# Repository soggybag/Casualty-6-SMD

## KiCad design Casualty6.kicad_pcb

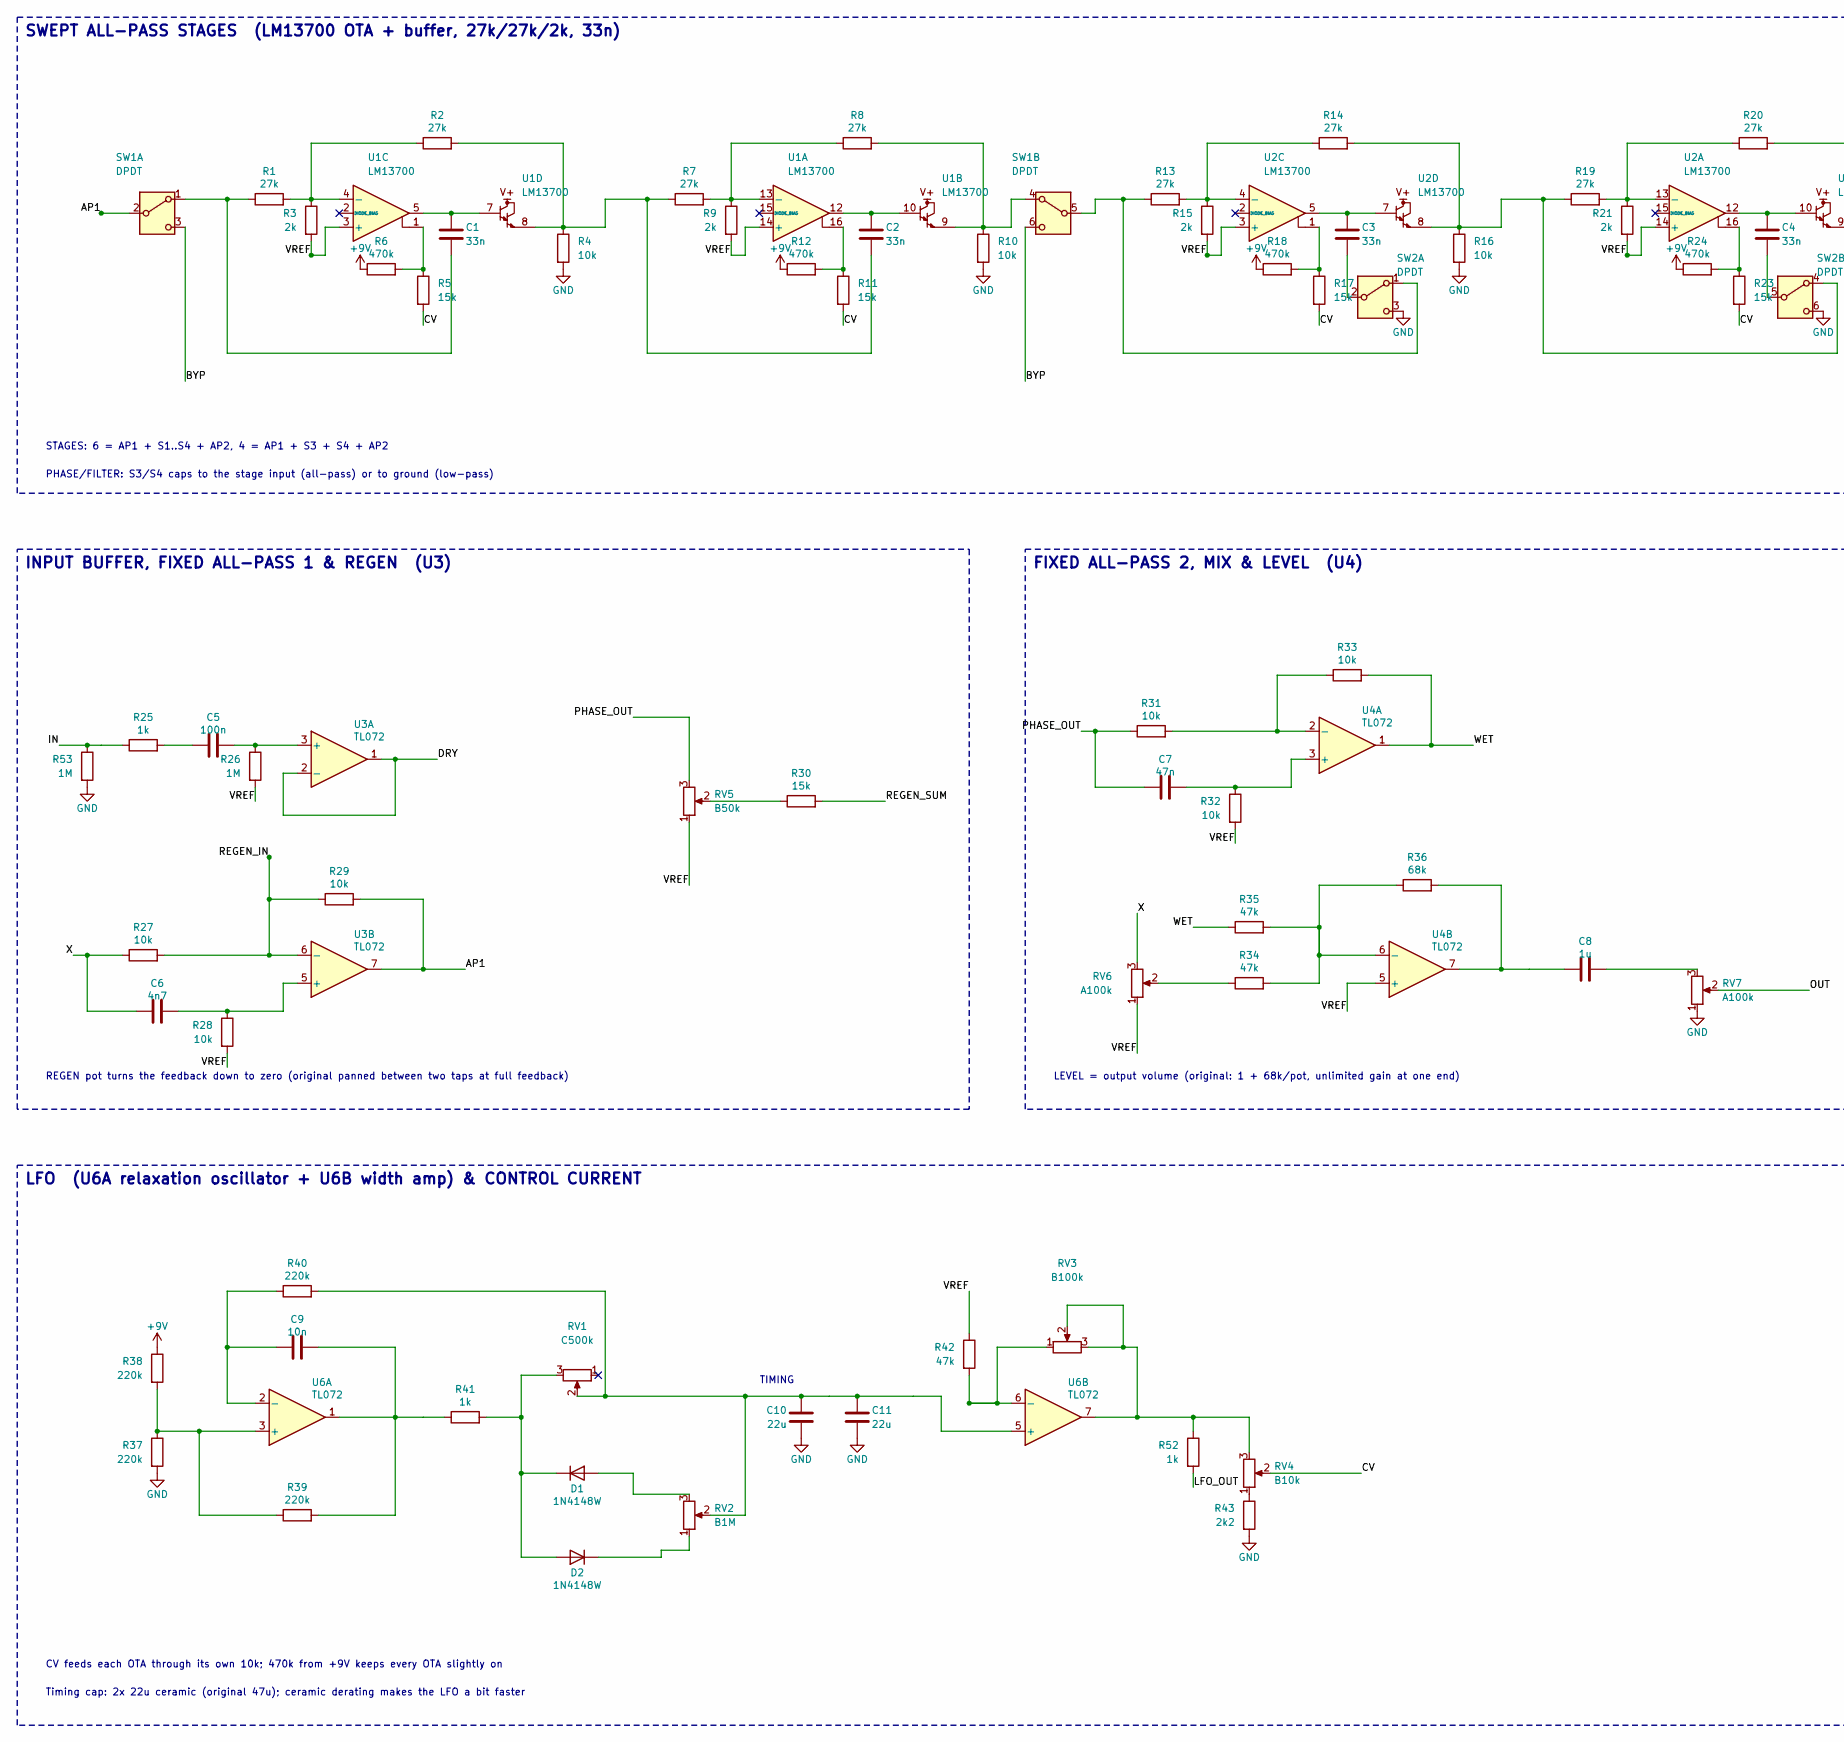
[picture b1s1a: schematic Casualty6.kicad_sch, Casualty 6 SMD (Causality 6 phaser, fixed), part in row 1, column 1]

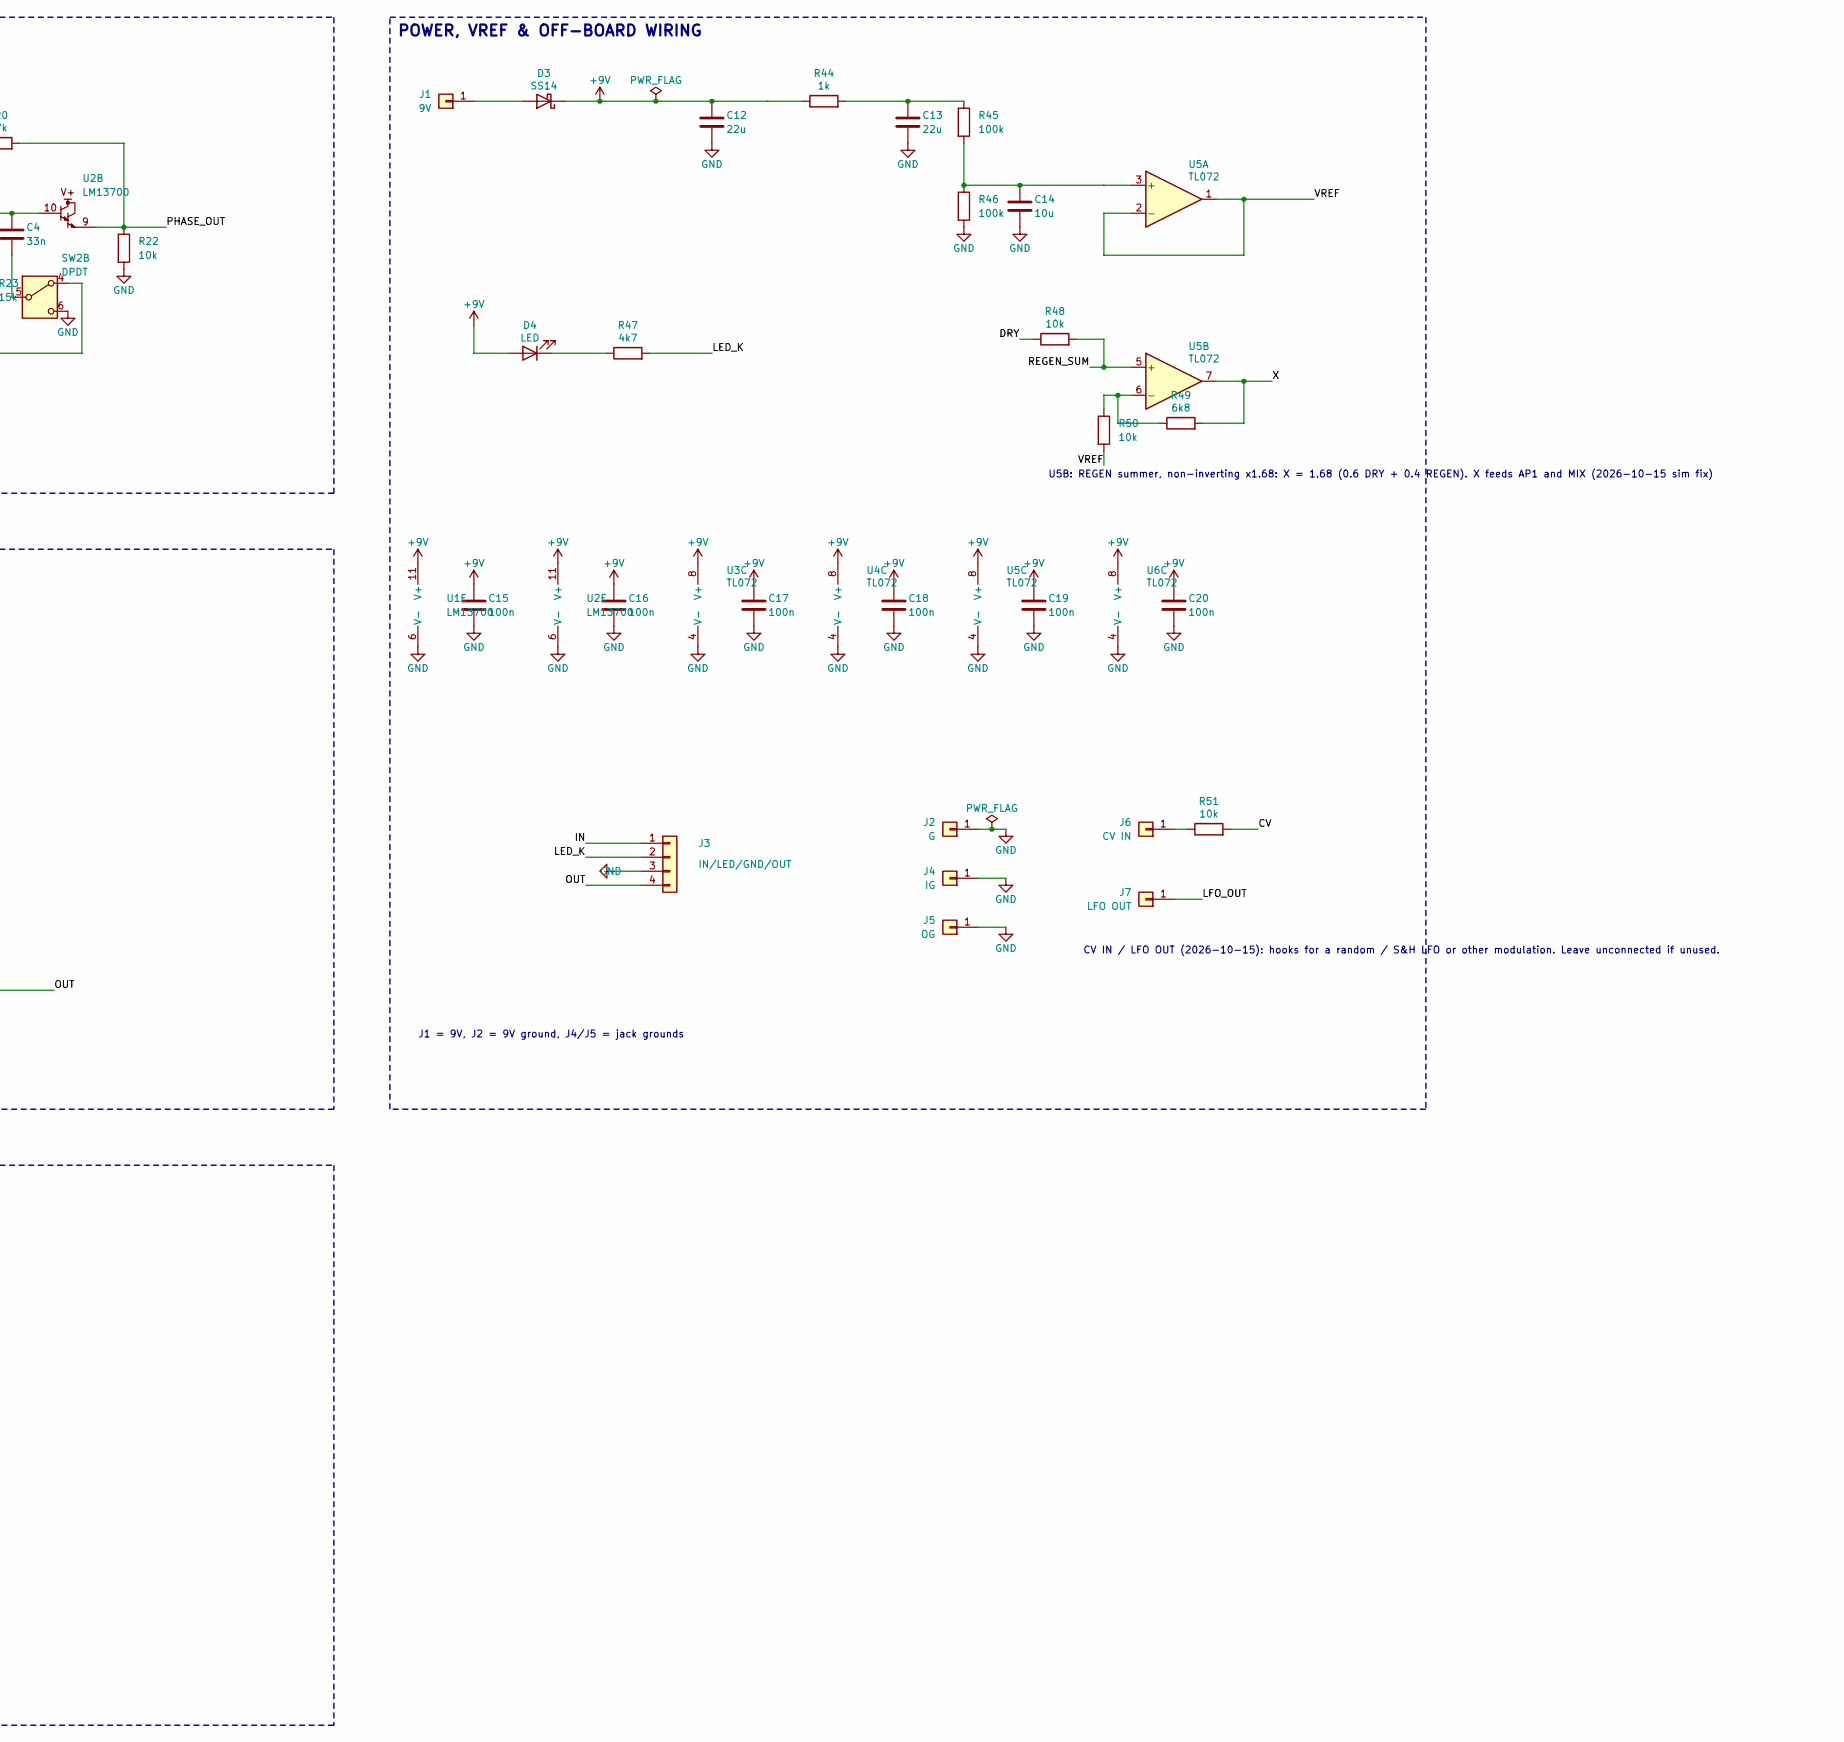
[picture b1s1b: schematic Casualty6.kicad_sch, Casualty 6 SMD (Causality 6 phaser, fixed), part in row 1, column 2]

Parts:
C1, C2, C3, C4: 33n; C_0805_2012Metric_Pad1.18x1.45mm_HandSolder; LCSC C1739
C5, C15, C16, C17, C18, C19, C20: 100n; C_0805_2012Metric_Pad1.18x1.45mm_HandSolder; LCSC C49678
C6: 4n7; C_0805_2012Metric_Pad1.18x1.45mm_HandSolder; LCSC C1744
C7: 47n; C_0805_2012Metric_Pad1.18x1.45mm_HandSolder; LCSC C53134
C8: 1u; C_0805_2012Metric_Pad1.18x1.45mm_HandSolder; LCSC C28323
C9: 10n; C_0805_2012Metric_Pad1.18x1.45mm_HandSolder; LCSC C1710
C10, C11, C12, C13: 22u; C_1206_3216Metric_Pad1.33x1.80mm_HandSolder; LCSC C12891
C14: 10u; C_0805_2012Metric_Pad1.18x1.45mm_HandSolder; LCSC C15850
D1, D2: 1N4148W; D_SOD-123; LCSC C81598
D3: SS14; D_SMA_Handsoldering; LCSC C2480
D4: LED; LED_D3.0mm
J1: 9V; SolderWire-0.5sqmm_1x01_D0.9mm_OD2.1mm
J2: G; SolderWire-0.5sqmm_1x01_D0.9mm_OD2.1mm
J3: IN/LED/GND/OUT; PinHeader_1x04_P2.54mm_Vertical
J4: IG; SolderWire-0.5sqmm_1x01_D0.9mm_OD2.1mm
J5: OG; SolderWire-0.5sqmm_1x01_D0.9mm_OD2.1mm
J6: CV IN; SolderWire-0.5sqmm_1x01_D0.9mm_OD2.1mm
J7: LFO OUT; SolderWire-0.5sqmm_1x01_D0.9mm_OD2.1mm
R1, R2, R7, R8, R13, R14, R19, R20: 27k; R_0805_2012Metric_Pad1.20x1.40mm_HandSolder; LCSC C17593
R3, R9, R15, R21: 2k; R_0805_2012Metric_Pad1.20x1.40mm_HandSolder; LCSC C17604
R4, R10, R16, R22, R27, R28, R29, R31, R32, R33, R48, R50, R51: 10k; R_0805_2012Metric_Pad1.20x1.40mm_HandSolder; LCSC C17414
R5, R11, R17, R23, R30: 15k; R_0805_2012Metric_Pad1.20x1.40mm_HandSolder; LCSC C17475
R6, R12, R18, R24: 470k; R_0805_2012Metric_Pad1.20x1.40mm_HandSolder; LCSC C17709
R25, R41, R44, R52: 1k; R_0805_2012Metric_Pad1.20x1.40mm_HandSolder; LCSC C17513
R26, R53: 1M; R_0805_2012Metric_Pad1.20x1.40mm_HandSolder; LCSC C17514
R34, R35, R42: 47k; R_0805_2012Metric_Pad1.20x1.40mm_HandSolder; LCSC C17713
R36: 68k; R_0805_2012Metric_Pad1.20x1.40mm_HandSolder; LCSC C17801
R37, R38, R39, R40: 220k; R_0805_2012Metric_Pad1.20x1.40mm_HandSolder; LCSC C17556
R43: 2k2; R_0805_2012Metric_Pad1.20x1.40mm_HandSolder; LCSC C17520
R45, R46: 100k; R_0805_2012Metric_Pad1.20x1.40mm_HandSolder; LCSC C149504
R47: 4k7; R_0805_2012Metric_Pad1.20x1.40mm_HandSolder; LCSC C17673
R49: 6k8; R_0805_2012Metric_Pad1.20x1.40mm_HandSolder; LCSC C17772
RV1: C500k; Potentiometer_Alpha_16mm_Vertical
RV2: B1M; Potentiometer_Alpha_16mm_Vertical
RV3: B100k; Potentiometer_Alpha_16mm_Vertical
RV4: B10k; Potentiometer_Alpha_16mm_Vertical
RV5: B50k; Potentiometer_Alpha_16mm_Vertical
RV6, RV7: A100k; Potentiometer_Alpha_16mm_Vertical
SW1, SW2: DPDT; SW_Taiway_100_DPDT_PC
U1, U2: LM13700; SOIC-16_3.9x9.9mm_P1.27mm; LCSC C1346265
U3, U4, U5, U6: TL072; SOIC-8_3.9x4.9mm_P1.27mm; LCSC C6961

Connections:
/AP1: R29.2, SW1.2 (B), U3.7
/BYP: SW1.3 (C), SW1.6 (C)
/CV: R5.2, R11.2, R17.2, R23.2, R51.2, RV4.2
/DRY: R48.1, U3.1, U3.2 (-)
/IN: J3.1, R25.1, R53.1
/LED_K: J3.2, R47.2
/LFO_OUT: J7.1, R52.2
/OUT: J3.4, RV7.2
/PHASE_OUT: C7.1, R20.2, R22.1, R31.1, RV5.3, U2.9
/REGEN_IN: R27.2, R29.1, U3.6 (-)
/REGEN_SUM: R30.2, R48.2, U5.5 (+)
/VREF: R3.2, R9.2, R15.2, R21.2, R26.2, R28.2, R32.2, R42.1, R50.2, RV5.1, RV6.1, U1.3 (+), U1.14 (+), U2.3 (+), U2.14 (+), U4.5 (+), U5.1, U5.2 (-)
/WET: R33.2, R35.1, U4.1
/X: C6.1, R27.1, R49.2, RV6.3, U5.7
unnamed: C1.1, U1.5, U1.7
unnamed: C2.1, U1.10, U1.12
unnamed: C2.2, R2.2, R4.1, R7.1, U1.8
unnamed: C3.1, U2.5, U2.7
unnamed: C4.1, U2.10, U2.12
unnamed: C5.1, R25.2
unnamed: C8.1, R36.2, U4.7
unnamed: C8.2, RV7.3
unnamed: C9.2, R39.2, R41.1, U6.1
unnamed: C13.1, R44.2, R45.1
unnamed: D1.2 (A), RV2.3
unnamed: D1.1 (K), D2.2 (A), R41.2, RV1.3
unnamed: D2.1 (K), RV2.1
unnamed: D3.2 (A), J1.1
unnamed: D4.1 (K), R47.1
unnamed: J6.1, R51.1
unnamed: R5.1, R6.2, U1.1
unnamed: R11.1, R12.2, U1.16
unnamed: R17.1, R18.2, U2.1
unnamed: R23.1, R24.2, U2.16
unnamed: R30.1, RV5.2
unnamed: R34.1, RV6.2
unnamed: R43.1, RV4.1
unnamed: R52.1, RV3.2, RV3.3, RV4.3, U6.7
unnamed: C1.2, R1.1, SW1.1 (A)
unnamed: R8.2, R10.1, SW1.4 (A), U1.9
unnamed: R13.1, SW1.5 (B), SW2.1 (A)
unnamed: C3.2, SW2.2 (B)
unnamed: R14.2, R16.1, R19.1, SW2.4 (A), U2.8
unnamed: C4.2, SW2.5 (B)
unnamed: R7.2, R8.1, R9.1, U1.13 (-)
unnamed: R1.2, R2.1, R3.1, U1.4 (-)
unnamed: R19.2, R20.1, R21.1, U2.13 (-)
unnamed: R13.2, R14.1, R15.1, U2.4 (-)
unnamed: C5.2, R26.1, U3.3 (+)
unnamed: C6.2, R28.1, U3.5 (+)
unnamed: C7.2, R32.1, U4.3 (+)
unnamed: R31.2, R33.1, U4.2 (-)
unnamed: R34.2, R35.2, R36.1, U4.6 (-)
unnamed: C14.1, R45.2, R46.1, U5.3 (+)
unnamed: R49.1, R50.1, U5.6 (-)
unnamed: R37.1, R38.2, R39.1, U6.3 (+)
unnamed: C9.1, R40.1, U6.2 (-)
unnamed: C10.1, C11.1, R40.2, RV1.2, RV2.2, U6.5 (+)
unnamed: R42.2, RV3.1, U6.6 (-)

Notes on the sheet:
CV IN / LFO OUT (2026-10-15): hooks for a random / S&H LFO or other modulation. Leave unconnected if unused.
SWEPT ALL-PASS STAGES (LM13700 OTA + buffer, 27k/27k/2k, 33n)
STAGES: 6 = AP1 + S1..S4 + AP2, 4 = AP1 + S3 + S4 + AP2
PHASE/FILTER: S3/S4 caps to the stage input (all-pass) or to ground (low-pass)
INPUT BUFFER, FIXED ALL-PASS 1 & REGEN (U3)
REGEN pot turns the feedback down to zero (original panned between two taps at full feedback)
FIXED ALL-PASS 2, MIX & LEVEL (U4)
LEVEL = output volume (original: 1 + 68k/pot, unlimited gain at one end)
LFO (U6A relaxation oscillator + U6B width amp) & CONTROL CURRENT
TIMING
CV feeds each OTA through its own 10k; 470k from +9V keeps every OTA slightly on
Timing cap: 2x 22u ceramic (original 47u); ceramic derating makes the LFO a bit faster
POWER, VREF & OFF-BOARD WIRING
U5B: REGEN summer, non-inverting x1.68: X = 1.68 (0.6 DRY + 0.4 REGEN). X feeds AP1 and MIX (2026-10-15 sim fix)
J1 = 9V, J2 = 9V ground, J4/J5 = jack grounds

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
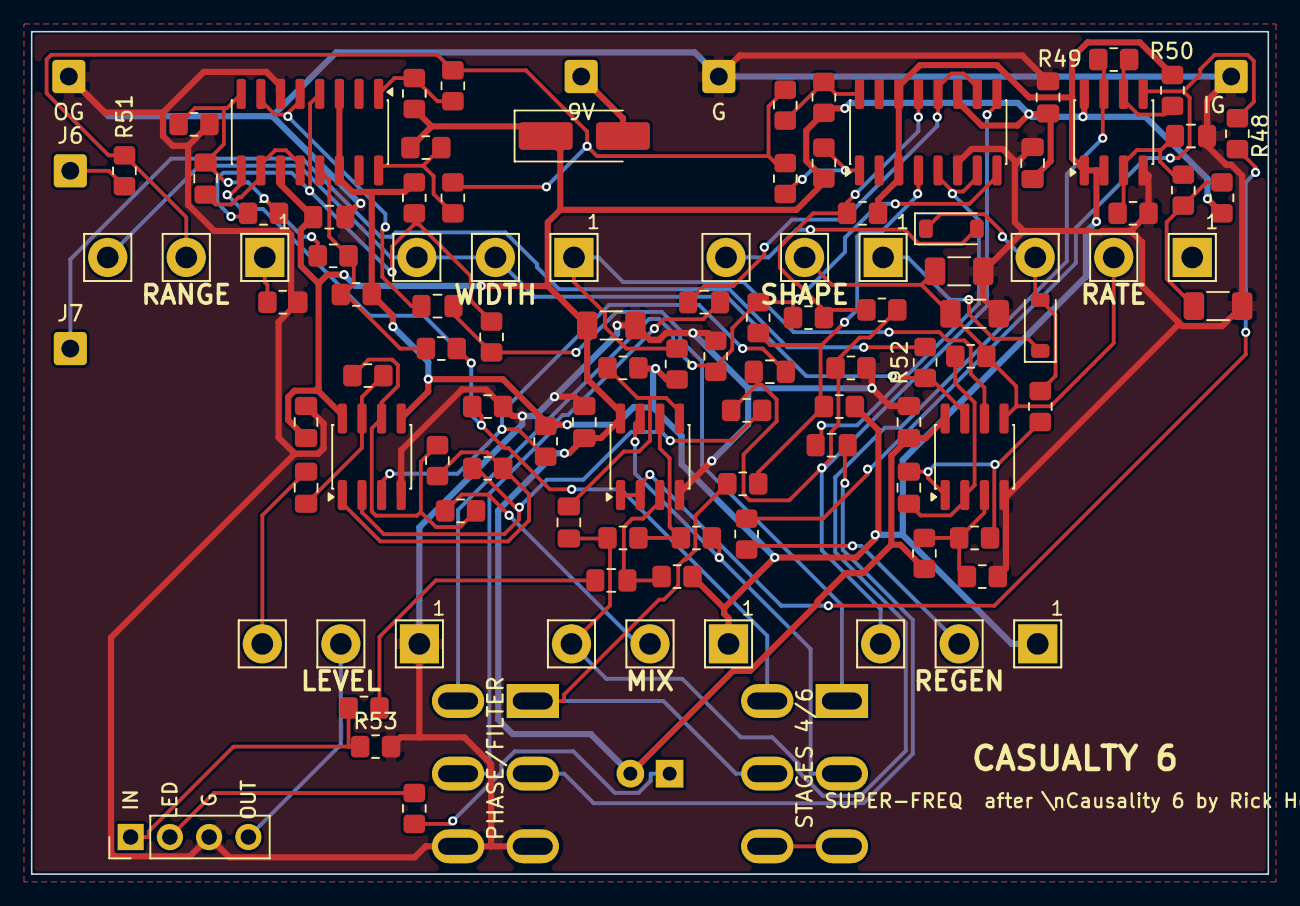
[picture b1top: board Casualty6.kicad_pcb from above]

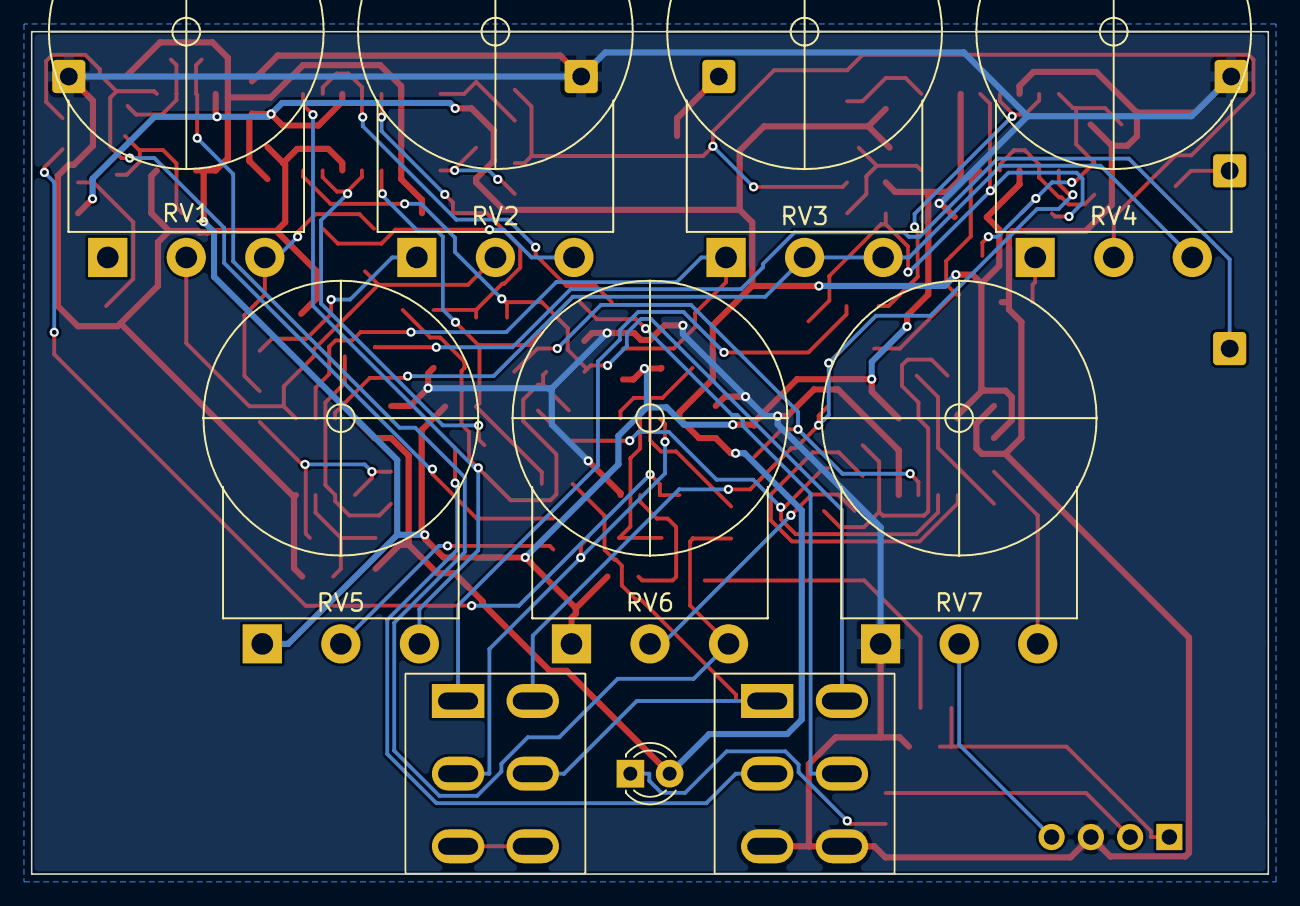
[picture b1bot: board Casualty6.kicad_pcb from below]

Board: 2 copper layers, 80.0 x 54.5 mm, 99 parts (3 on the bottom side), 61 nets.
